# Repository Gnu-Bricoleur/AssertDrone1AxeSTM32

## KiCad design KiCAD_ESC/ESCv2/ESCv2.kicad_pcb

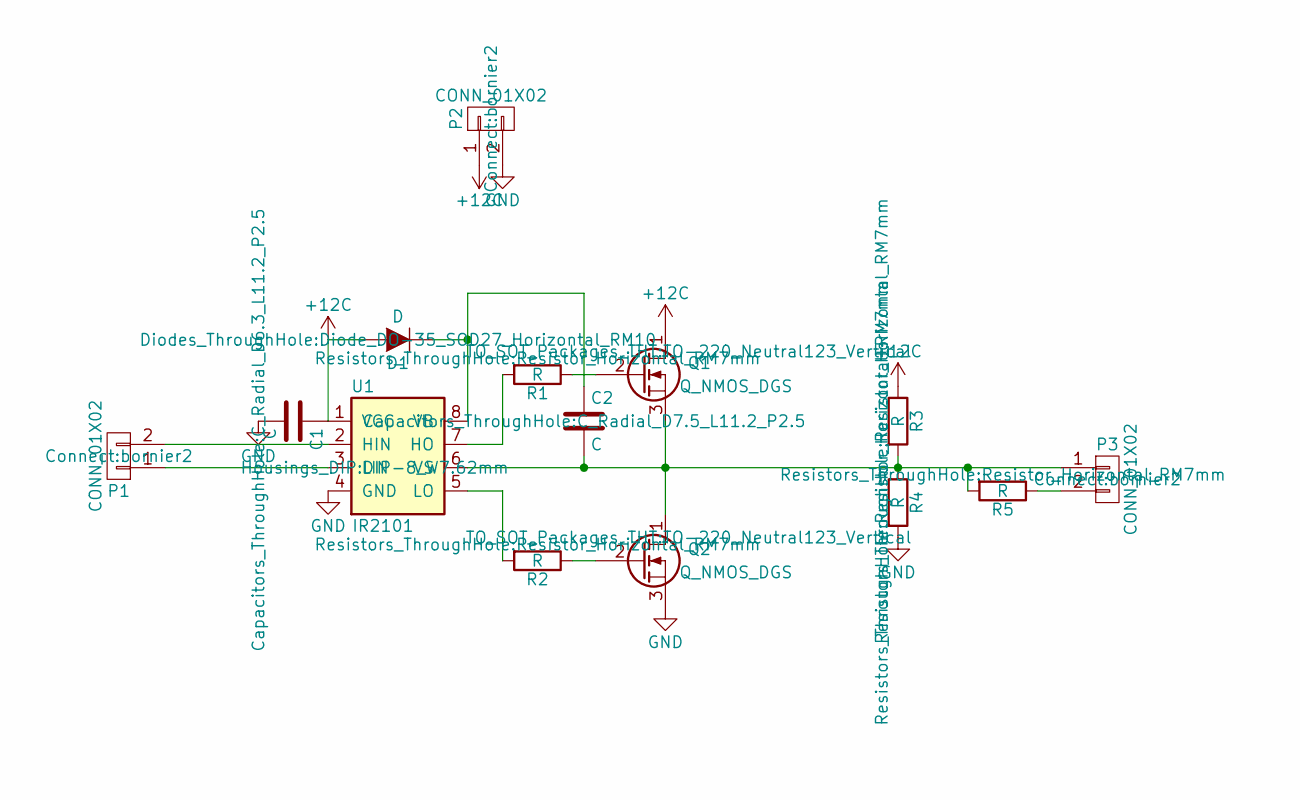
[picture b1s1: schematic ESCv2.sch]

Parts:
C1: C; C_Radial_D6.3_L11.2_P2.5
C2: C; C_Radial_D7.5_L11.2_P2.5
D1: D; Diode_DO-35_SOD27_Horizontal_RM10
P1, P2, P3: CONN_01X02; bornier2
Q1, Q2: Q_NMOS_DGS; TO-220_Neutral123_Vertical
R1, R2, R3, R4, R5: R; Resistor_Horizontal_RM7mm
U1: IR2101; DIP-8_W7.62mm

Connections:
+12C: C1.1, D1.2 (A), P2.1, Q1.1 (D), R3.1, U1.1 (VCC)
GND: C1.2, P2.2, Q2.3 (S), R4.2, U1.4 (GND)
unnamed: C2.1, D1.1 (K), U1.8 (VB)
unnamed: C2.2, P3.1, Q1.3 (S), Q2.1 (D), R3.2, R4.1, R5.2, U1.6 (VS)
unnamed: P1.1, U1.3 (LIN)
unnamed: P1.2, U1.2 (HIN)
unnamed: P3.2, R5.1
unnamed: Q1.2 (G), R1.1
unnamed: Q2.2 (G), R2.1
unnamed: R1.2, U1.7 (HO)
unnamed: R2.2, U1.5 (LO)

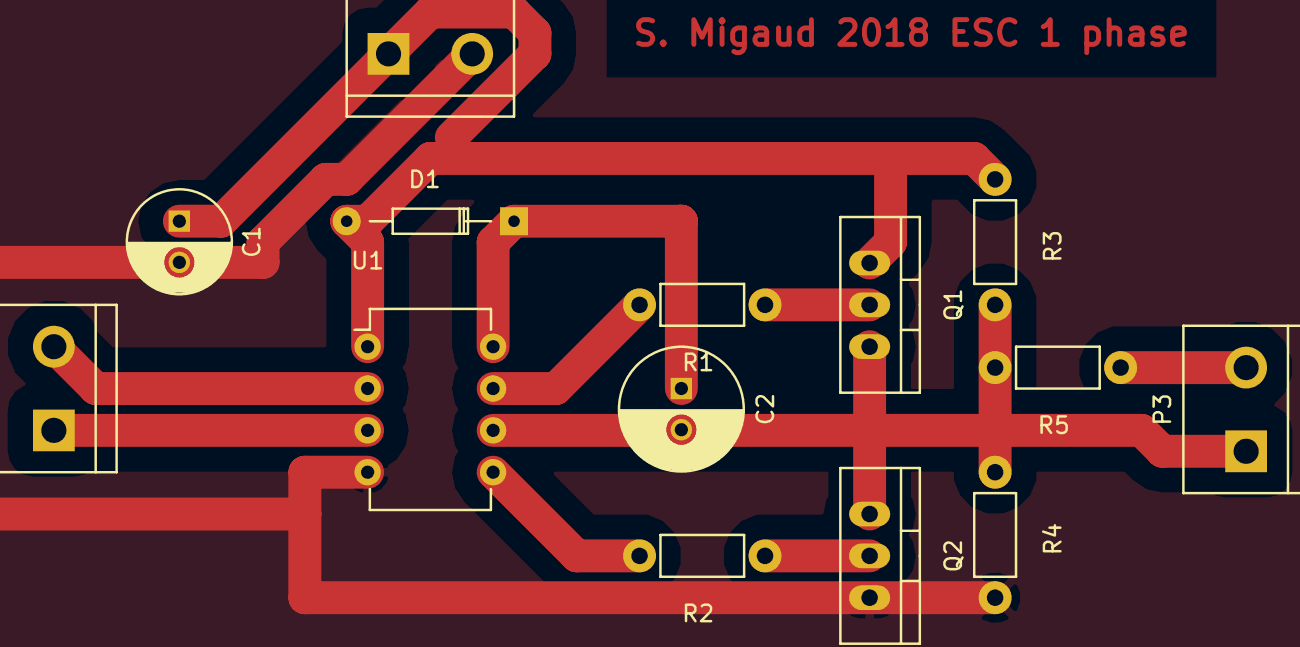
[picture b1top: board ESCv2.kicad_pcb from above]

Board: 2 copper layers, 14 parts (0 on the bottom side), 11 nets.

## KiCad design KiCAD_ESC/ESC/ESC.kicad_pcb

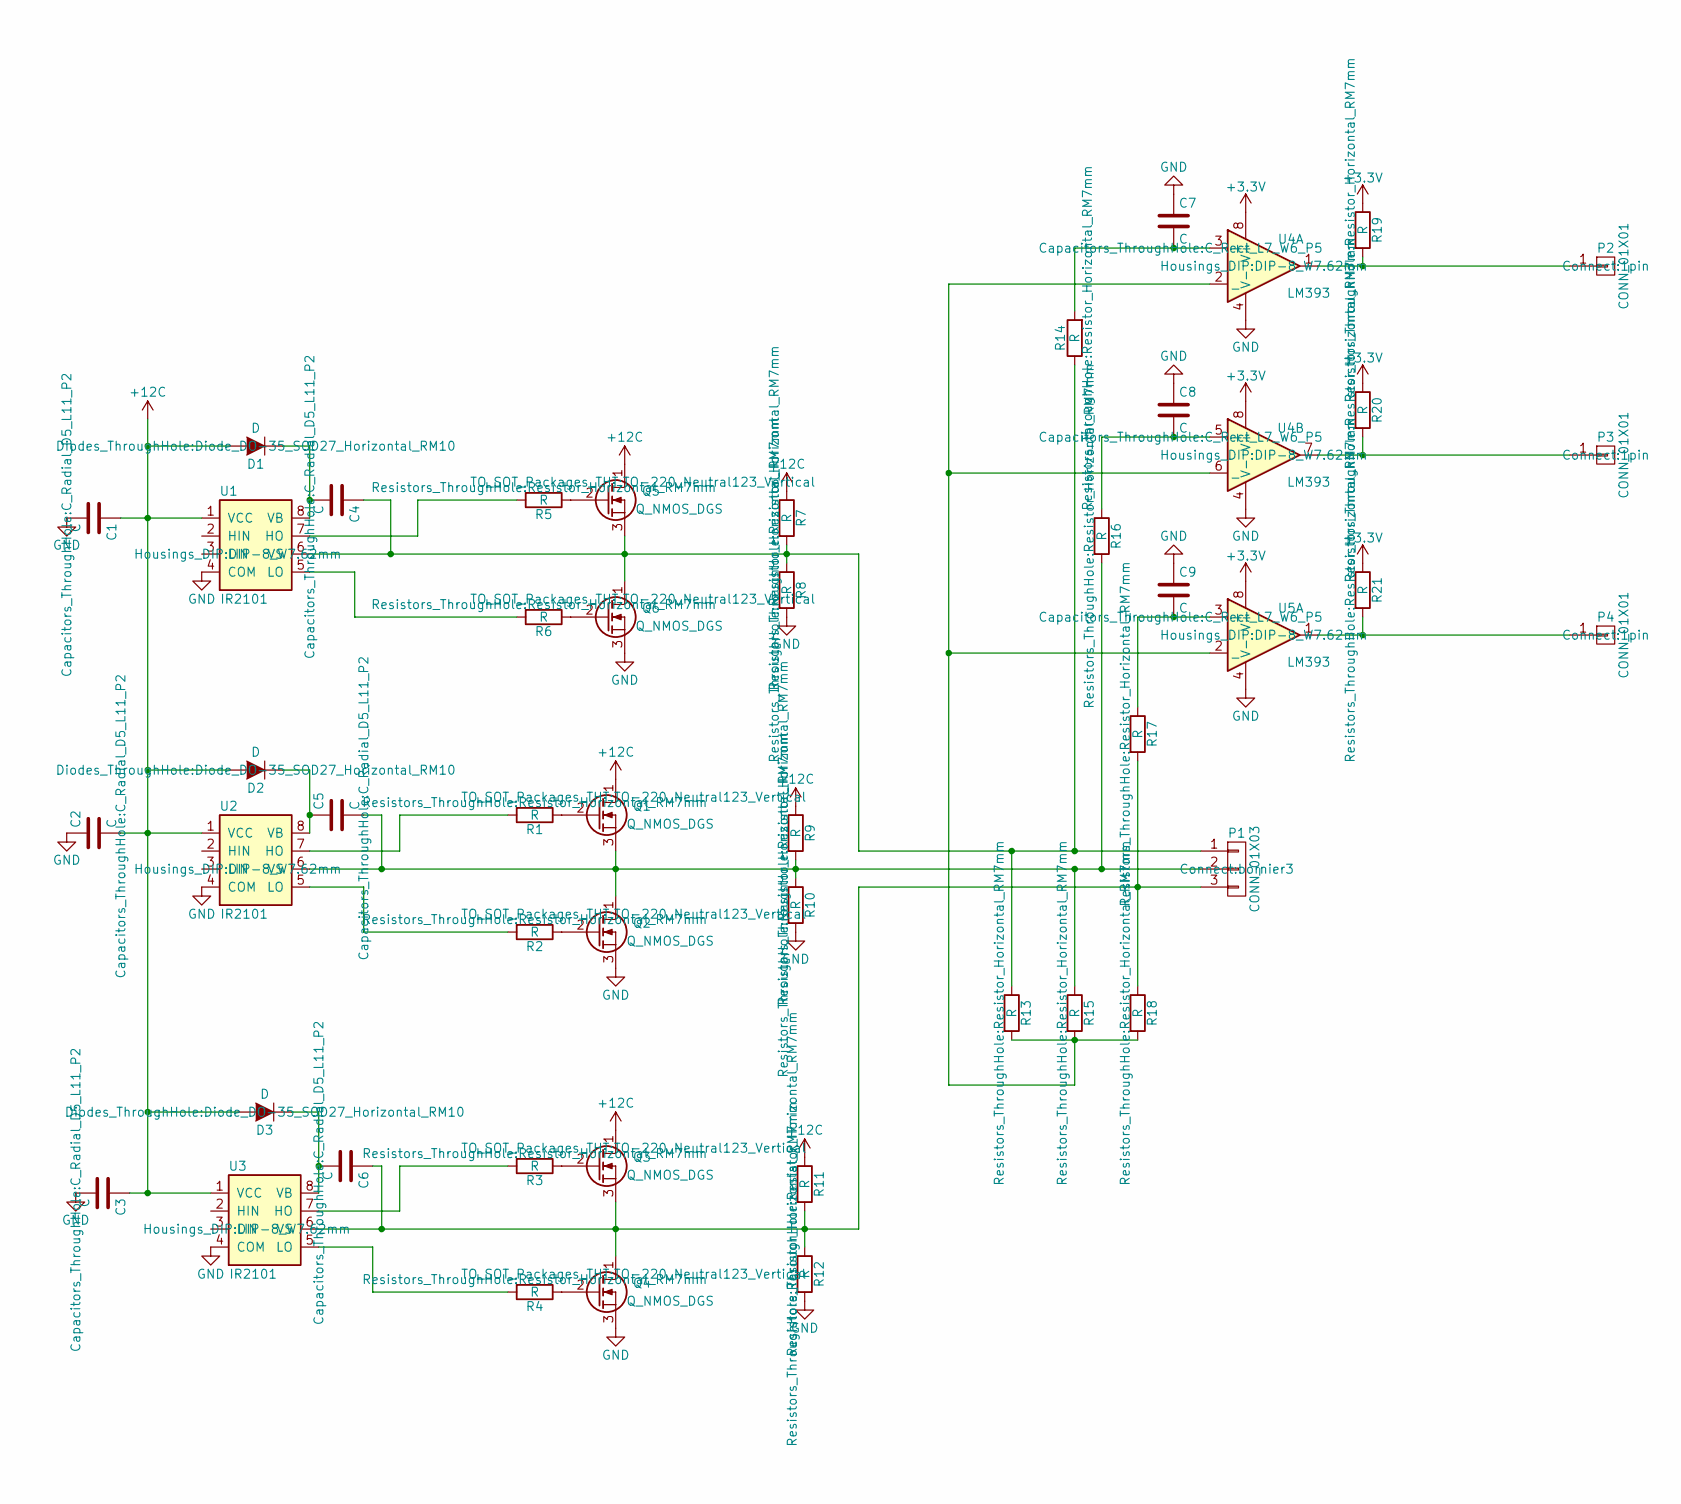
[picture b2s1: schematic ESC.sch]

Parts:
C1, C2, C3, C4, C5, C6: C; C_Radial_D5_L11_P2
C7, C8, C9: C; C_Rect_L7_W6_P5
D1, D2, D3: D; Diode_DO-35_SOD27_Horizontal_RM10
P1: CONN_01X03; bornier3
P2, P3, P4: CONN_01X01; 1pin
Q1, Q2, Q3, Q4, Q5, Q6: Q_NMOS_DGS; TO-220_Neutral123_Vertical
R1, R2, R3, R4, R5, R6, R7, R8, R9, R10, R11, R12, R13, R14, R15, R16, R17, R18, R19, R20, R21: R; Resistor_Horizontal_RM7mm
U1, U2, U3: IR2101; DIP-8_W7.62mm
U4, U5: LM393; DIP-8_W7.62mm

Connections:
+3V3: R19.1, R20.1, R21.1, U4.8 (V+), U5.8 (V+)
+12C: C1.1, C2.2, C3.1, D1.2 (A), D2.2 (A), D3.2 (A), Q1.1 (D), Q3.1 (D), Q5.1 (D), R7.1, R9.1, R11.1, U1.1 (VCC), U2.1 (VCC), U3.1 (VCC)
GND: C1.2, C2.1, C3.2, C7.1, C8.1, C9.1, Q2.3 (S), Q4.3 (S), Q6.3 (S), R8.2, R10.2, R12.2, U1.4 (COM), U2.4 (COM), U3.4 (COM), U4.4 (V-), U5.4 (V-)
unnamed: C4.1, P1.1, Q5.3 (S), Q6.1 (D), R7.2, R8.1, R13.1, R14.1, U1.6 (VS)
unnamed: C4.2, D1.1 (K), U1.8 (VB)
unnamed: C5.1, D2.1 (K), U2.8 (VB)
unnamed: C5.2, P1.2, Q1.3 (S), Q2.1 (D), R9.2, R10.1, R15.1, R16.2, U2.6 (VS)
unnamed: C6.1, P1.3, Q3.3 (S), Q4.1 (D), R11.2, R12.1, R17.2, R18.1, U3.6 (VS)
unnamed: C6.2, D3.1 (K), U3.8 (VB)
unnamed: C7.2, R14.2, U4.3 (+)
unnamed: C8.2, R16.1, U4.5 (+)
unnamed: C9.2, R17.1, U5.3 (+)
unnamed: P2.1, R19.2, U4.1
unnamed: P3.1, R20.2, U4.7
unnamed: P4.1, R21.2, U5.1
unnamed: Q1.2 (G), R1.1
unnamed: Q2.2 (G), R2.1
unnamed: Q3.2 (G), R3.1
unnamed: Q4.2 (G), R4.1
unnamed: Q5.2 (G), R5.1
unnamed: Q6.2 (G), R6.1
unnamed: R1.2, U2.7 (HO)
unnamed: R2.2, U2.5 (LO)
unnamed: R3.2, U3.7 (HO)
unnamed: R4.2, U3.5 (LO)
unnamed: R5.2, U1.7 (HO)
unnamed: R6.2, U1.5 (LO)
unnamed: R13.2, R15.2, R18.2, U4.2 (_), U4.6 (_), U5.2 (_)

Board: 2 copper layers, 48 parts (0 on the bottom side), 28 nets, no tracks yet.

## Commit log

2018-06-06 Commit initial
2018-06-06 ajout de la lecture de l'angle a la plaace de l'acceleration
2018-06-06 ajout PWM etape 1
2018-06-06 ajout PWM etape 2
2018-06-06 ajout PWM etape 3
2018-06-08 vendredi soir, l'assert marche ! reste a regler les coefs
2018-06-08 PPPPCCCCCCCCCCCCCCCCCCCCCCCCCCBBBBBBBBBBBgit statusgit statusgit status
2018-06-11 debut serieux de gerber
2018-06-14 kicad de mieux en mieux
